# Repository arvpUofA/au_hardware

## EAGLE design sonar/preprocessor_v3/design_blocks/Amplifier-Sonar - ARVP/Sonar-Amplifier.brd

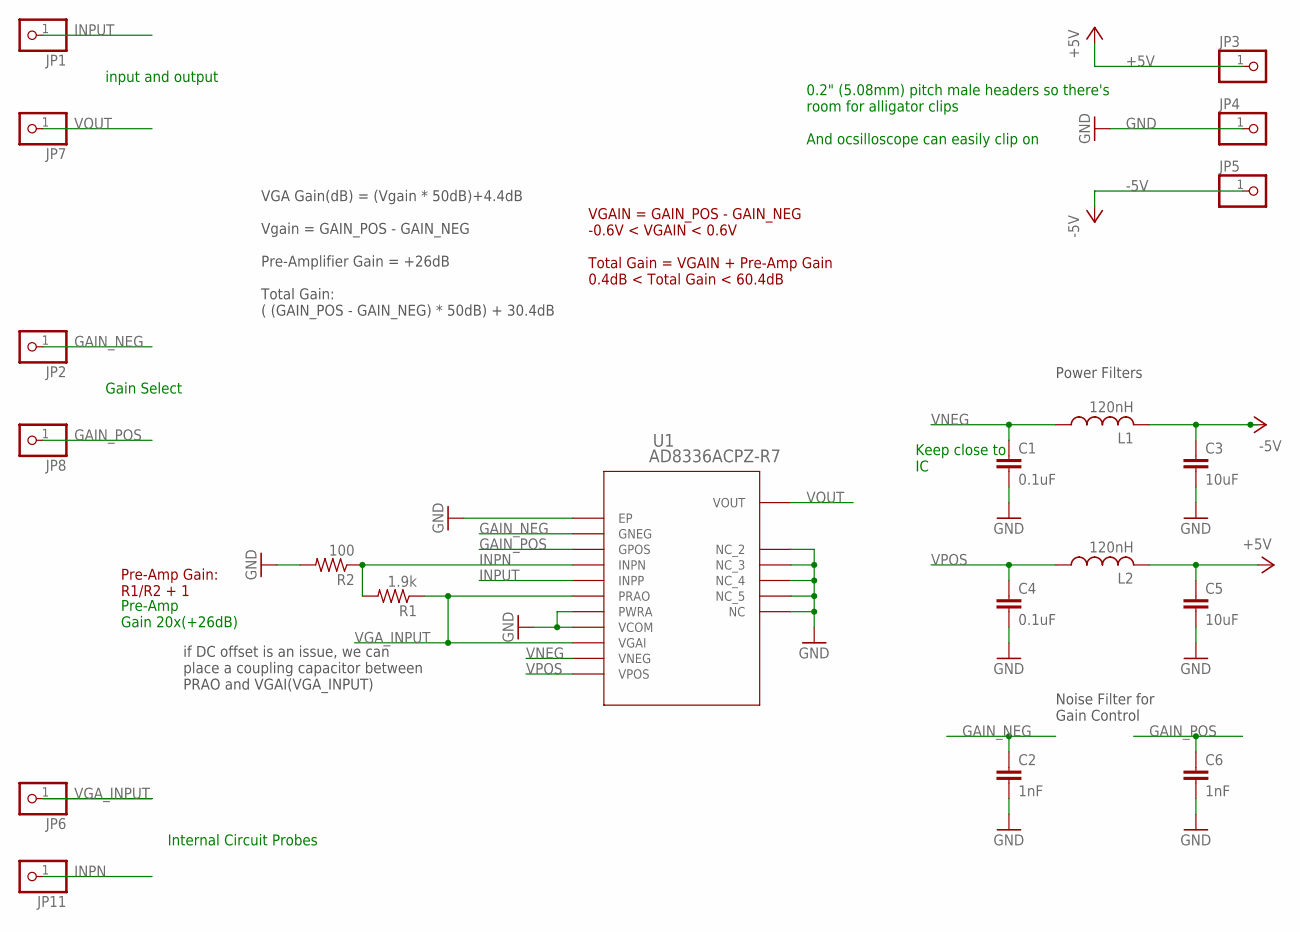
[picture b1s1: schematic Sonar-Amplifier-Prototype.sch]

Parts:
C1, C4: 0.1uF; C0603
C2, C6: 1nF; C0603
C3, C5: 10uF; C1206
JP1, JP2, JP3, JP4, JP5, JP6, JP7, JP8, JP11: PINHD-1X1; 1X01
L1, L2: 120nH; L3225P
R1: 1.9k; R0603
R2: 100; R0603
U1: AD8336ACPZ-R7; CP_16_4

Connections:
+5V: C5.1, JP3.1, L2.2
-5V: C3.1, JP5.1, L1.2
GAIN_NEG: C2.1, JP2.1, U1.GNEG
GAIN_POS: C6.1, JP8.1, U1.GPOS
GND: C1.2, C2.2, C3.2, C4.2, C5.2, C6.2, JP4.1, R2.2, U1.GND1 (EP), U1.NC, U1.NC1 (NC_2), U1.NC2 (NC_3), U1.NC3 (NC_4), U1.NC4 (NC_5), U1.PWRA, U1.VCOM
INPN: JP11.1, R1.2, R2.1, U1.INPN
INPUT: JP1.1, U1.INPP
VGA_INPUT: JP6.1, R1.1, U1.PRAO, U1.VGAI
VNEG: C1.1, L1.1, U1.VNEG
VOUT: JP7.1, U1.VOUT
VPOS: C4.1, L2.1, U1.VPOS

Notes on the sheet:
Pre-Amp Gain 20x(+26dB)
Power Filters
Keep close to IC
Noise Filter for Gain Control
0.2" (5.08mm) pitch male headers so there's room for alligator clips And ocsilloscope can easily clip on
input and output
Pre-Amp Gain: R1/R2 + 1
if DC offset is an issue, we can place a coupling capacitor between PRAO and VGAI(VGA_INPUT)
Gain Select
VGA Gain(dB) = (Vgain * 50dB)+4.4dB Vgain = GAIN_POS - GAIN_NEG Pre-Amplifier Gain = +26dB Total Gain: ( (GAIN_POS - GAIN_NEG) * 50dB) + 30.4dB
VGAIN = GAIN_POS - GAIN_NEG -0.6V < VGAIN < 0.6V Total Gain = VGAIN + Pre-Amp Gain 0.4dB < Total Gain < 60.4dB
Internal Circuit Probes

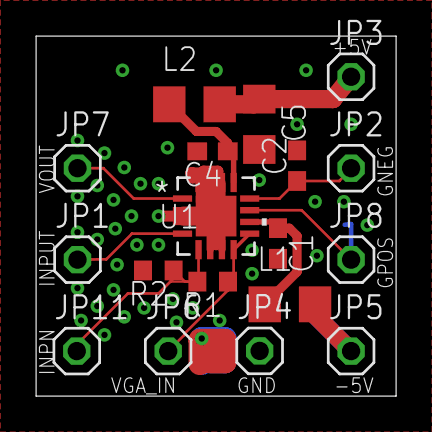
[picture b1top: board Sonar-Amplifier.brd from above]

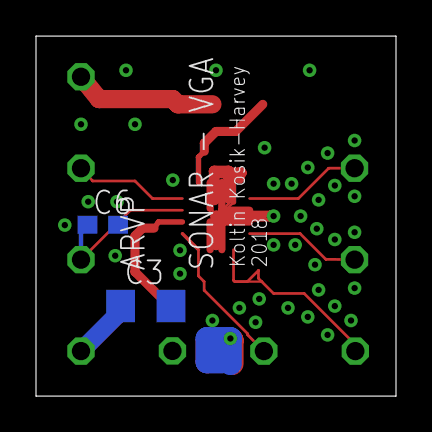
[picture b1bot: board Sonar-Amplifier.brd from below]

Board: 2 copper layers, 20.0 x 20.0 mm, 20 parts (2 on the bottom side), 11 nets.

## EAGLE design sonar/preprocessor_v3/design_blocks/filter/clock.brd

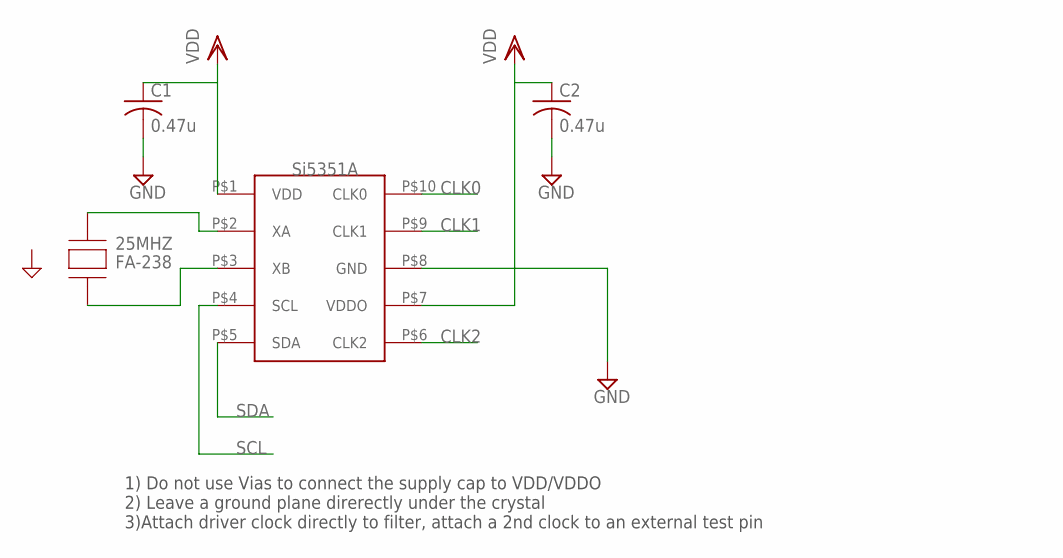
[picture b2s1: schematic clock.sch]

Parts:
25MHZ: FA-238
C1, C2: 0.47u; C0805
U$2: SI5351A; MSOP-10

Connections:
CLK0: U$2.P$10 (CLK0)
CLK1: U$2.P$9 (CLK1)
CLK2: U$2.P$6 (CLK2)
GND: C1.2, C2.2, U$2.P$8 (GND)
unnamed: 25MHZ.P$4 (XA), U$2.P$2 (XA)
unnamed: 25MHZ.P$2 (XB), U$2.P$3 (XB)
SCL: U$2.P$4 (SCL)
SDA: U$2.P$5 (SDA)
VDD: C1.1, C2.1, U$2.P$1 (VDD), U$2.P$7 (VDDO)

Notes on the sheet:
1) Do not use Vias to connect the supply cap to VDD/VDDO 2) Leave a ground plane direrectly under the crystal 3)Attach driver clock directly to filter, attach a 2nd clock to an external test pin

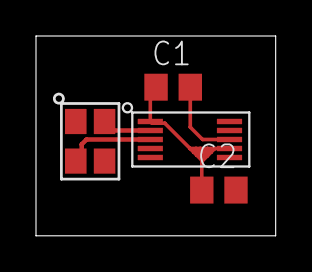
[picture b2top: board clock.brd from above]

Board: 2 copper layers, 13.3 x 11.1 mm, 4 parts (0 on the bottom side), 4 nets.

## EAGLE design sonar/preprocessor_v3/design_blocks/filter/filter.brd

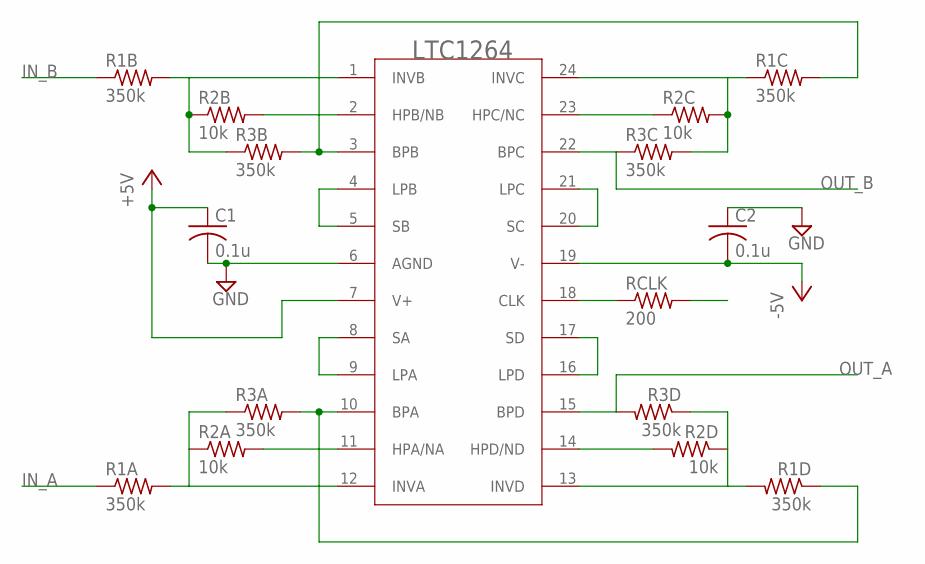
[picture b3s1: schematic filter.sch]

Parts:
C1, C2: 0.1u; C0805
R1A, R1B, R1C, R1D, R3A, R3B, R3C, R3D: 350k; R0805
R2A, R2B, R2C, R2D: 10k; R0805
RCLK: 200; R0805
U$1: LTC1264SMD; SO24W

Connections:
+5V: C1.1, U$1.7 (V+)
-5V: C2.2, U$1.19 (V-)
CLK: RCLK.2
GND: C1.2, C2.1, U$1.6 (AGND)
IN_A: R1A.1
IN_B: R1B.1
unnamed: R2D.2, U$1.14 (HPD/ND)
unnamed: R1D.2, R2D.1, R3D.1, U$1.13 (INVD)
unnamed: U$1.16 (LPD), U$1.17 (SD)
unnamed: R2C.1, U$1.23 (HPC/NC)
unnamed: R1C.1, R2C.2, R3C.2, U$1.24 (INVC)
unnamed: R2B.2, U$1.2 (HPB/NB)
unnamed: R1B.2, R2B.1, R3B.1, U$1.1 (INVB)
unnamed: U$1.4 (LPB), U$1.5 (SB)
unnamed: U$1.20 (SC), U$1.21 (LPC)
unnamed: RCLK.1, U$1.18 (CLK)
unnamed: R2A.2, U$1.11 (HPA/NA)
unnamed: U$1.8 (SA), U$1.9 (LPA)
unnamed: R1A.2, R2A.1, R3A.1, U$1.12 (INVA)
OUT_2ND_A: R1D.1, R3A.2, U$1.10 (BPA)
OUT_2ND_ORDER_B: R1C.2, R3B.2, U$1.3 (BPB)
OUT_A: R3D.2, U$1.15 (BPD)
OUT_B: R3C.1, U$1.22 (BPC)

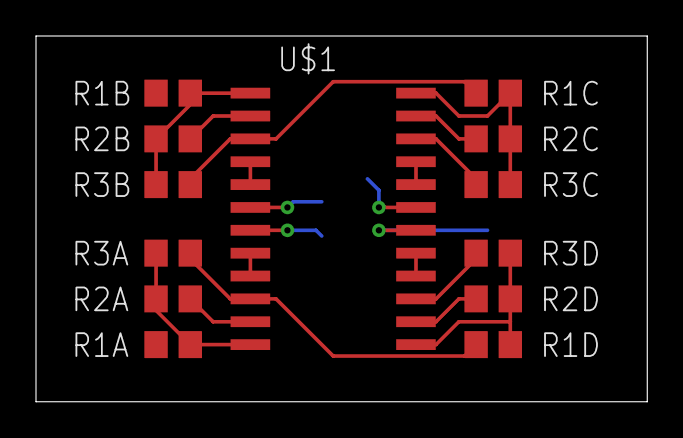
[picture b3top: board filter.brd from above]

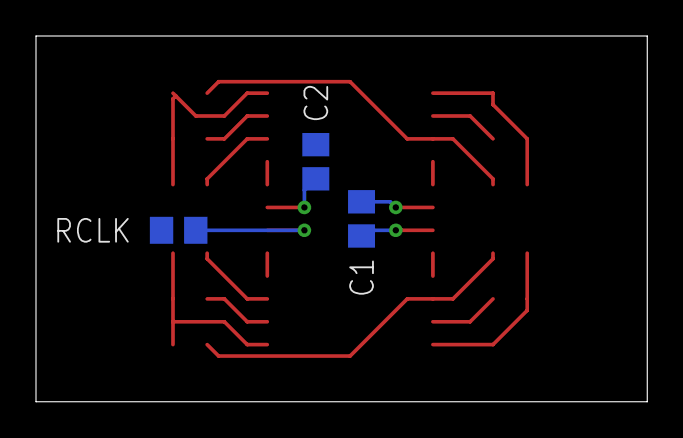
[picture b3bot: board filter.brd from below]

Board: 2 copper layers, 34.0 x 20.3 mm, 16 parts (3 on the bottom side), 20 nets.

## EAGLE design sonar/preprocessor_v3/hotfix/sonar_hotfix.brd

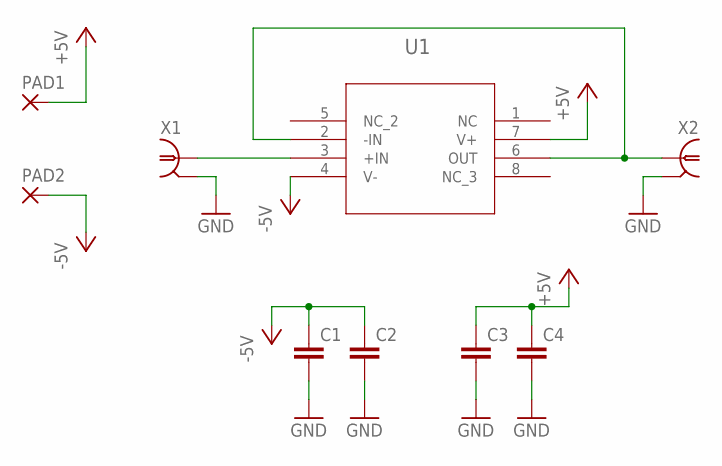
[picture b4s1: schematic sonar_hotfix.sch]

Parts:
C1, C2, C3, C4: C-EUC0603; C0603
PAD1, PAD2: WIREPADSMD5-2,5; 5-2,5
U1: LTC6240SO-8; SO-8
X1, X2: 0731000105

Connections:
+5V: C3.1, C4.1, PAD1.1, U1.7 (V+)
-5V: C1.1, C2.1, PAD2.1, U1.4 (V-)
GND: C1.2, C2.2, C3.2, C4.2, X1.P$1 (2), X1.P$2 (2), X2.P$1 (2), X2.P$2 (2)
unnamed: U1.3 (+IN), X1.P$3 (1)
unnamed: U1.2 (-IN), U1.6 (OUT), X2.P$3 (1)

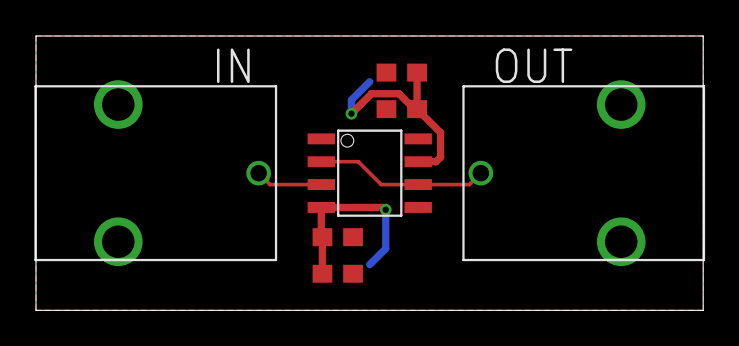
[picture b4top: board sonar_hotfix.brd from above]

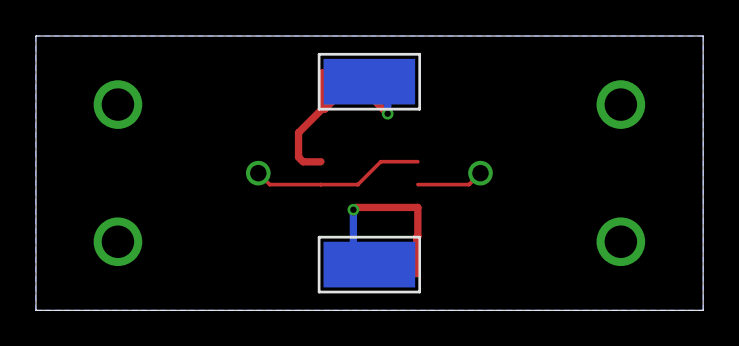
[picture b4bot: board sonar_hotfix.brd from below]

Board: 2 copper layers, 37.1 x 15.2 mm, 9 parts (2 on the bottom side), 5 nets.

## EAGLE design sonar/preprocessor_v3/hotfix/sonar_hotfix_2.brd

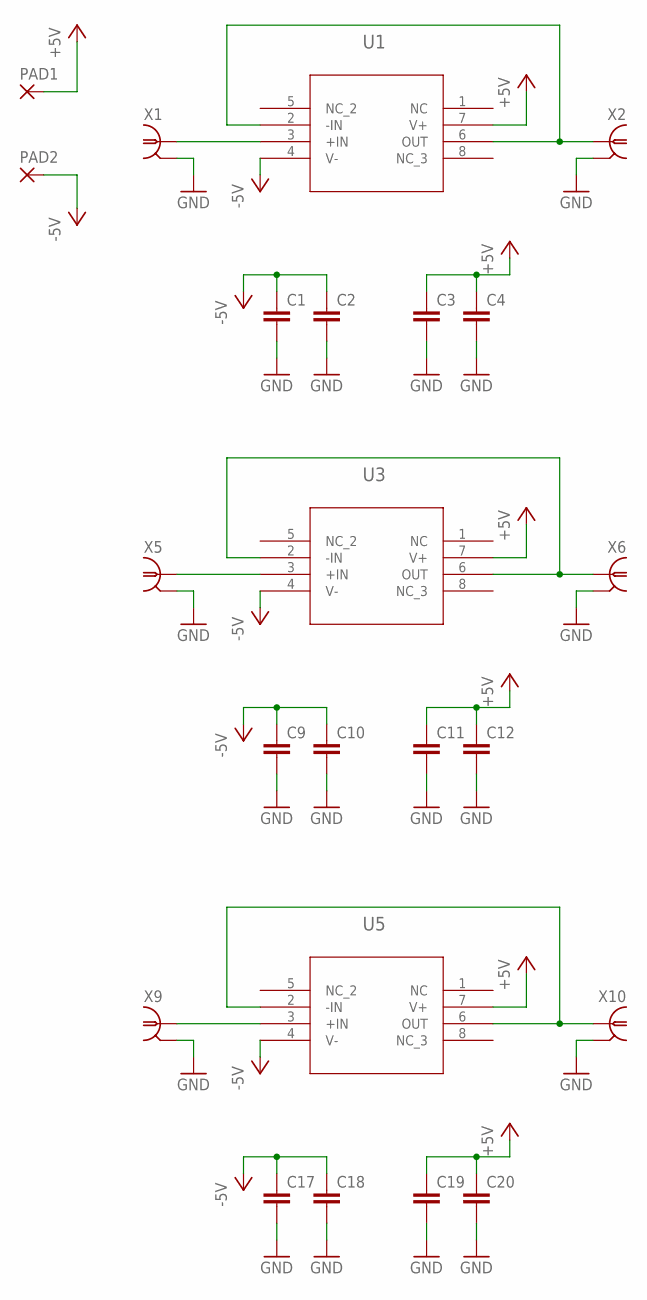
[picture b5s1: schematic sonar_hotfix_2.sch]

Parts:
C1, C2, C3, C4, C9, C10, C11, C12, C17, C18, C19, C20: C-EUC0603; C0603
PAD1, PAD2: WIREPADSMD5-2,5; 5-2,5
U1, U3, U5: LTC6240SO-8; SO-8
X1, X2, X5, X6, X9, X10: 0731000105

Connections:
+5V: C3.1, C4.1, C11.1, C12.1, C19.1, C20.1, PAD1.1, U1.7 (V+), U3.7 (V+), U5.7 (V+)
-5V: C1.1, C2.1, C9.1, C10.1, C17.1, C18.1, PAD2.1, U1.4 (V-), U3.4 (V-), U5.4 (V-)
GND: C1.2, C2.2, C3.2, C4.2, C9.2, C10.2, C11.2, C12.2, C17.2, C18.2, C19.2, C20.2, X1.P$1 (2), X1.P$2 (2), X2.P$1 (2), X2.P$2 (2), X5.P$1 (2), X5.P$2 (2), X6.P$1 (2), X6.P$2 (2), X9.P$1 (2), X9.P$2 (2), X10.P$1 (2), X10.P$2 (2)
unnamed: U1.3 (+IN), X1.P$3 (1)
unnamed: U1.2 (-IN), U1.6 (OUT), X2.P$3 (1)
unnamed: U3.3 (+IN), X5.P$3 (1)
unnamed: U3.2 (-IN), U3.6 (OUT), X6.P$3 (1)
unnamed: U5.3 (+IN), X9.P$3 (1)
unnamed: U5.2 (-IN), U5.6 (OUT), X10.P$3 (1)

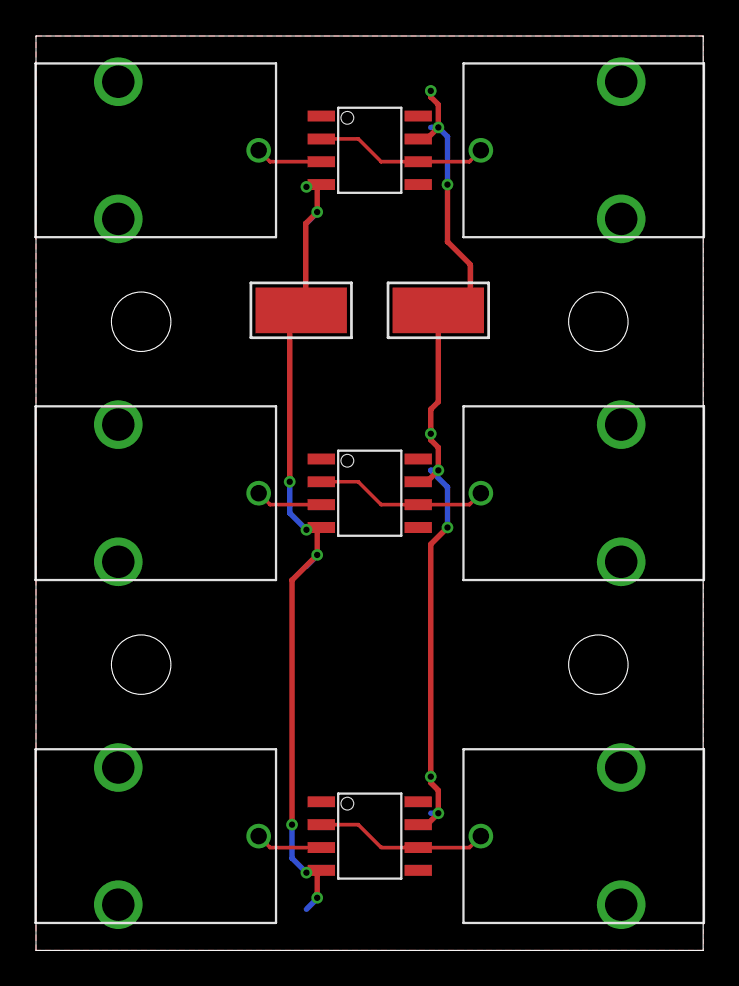
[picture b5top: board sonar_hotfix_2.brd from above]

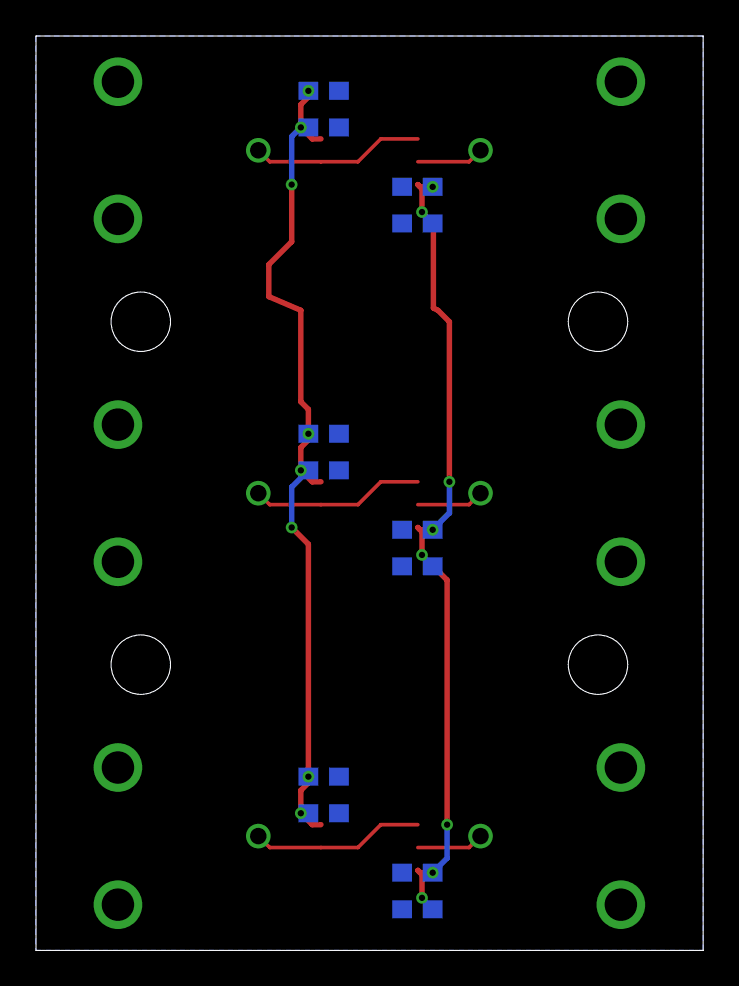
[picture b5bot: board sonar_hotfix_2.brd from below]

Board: 2 copper layers, 37.1 x 50.8 mm, 27 parts (12 on the bottom side), 9 nets.

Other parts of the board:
U$1, U$2, U$3, U$4: STAND-OFF

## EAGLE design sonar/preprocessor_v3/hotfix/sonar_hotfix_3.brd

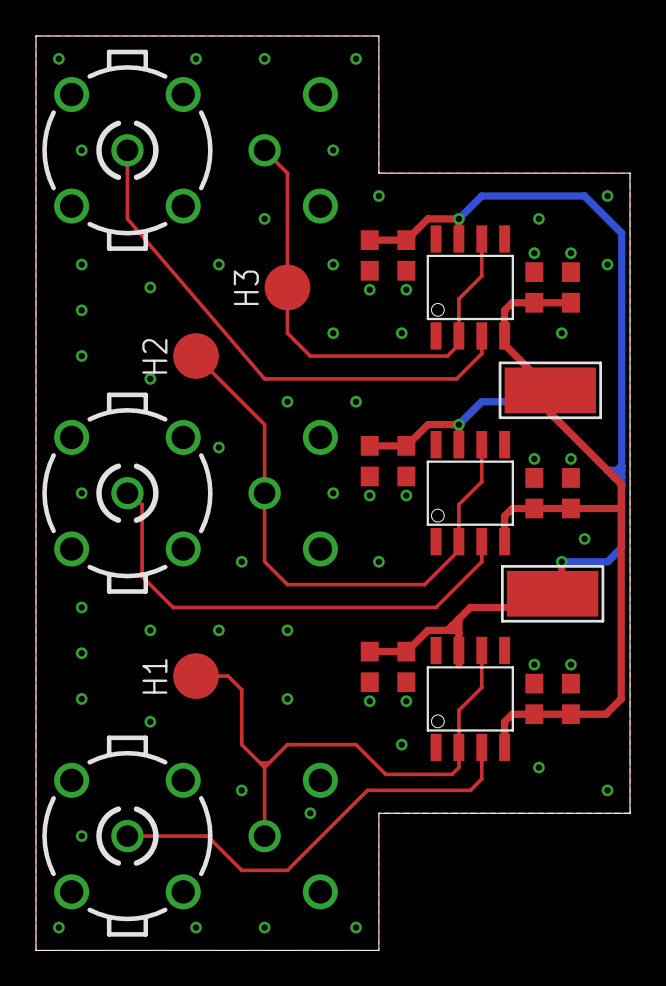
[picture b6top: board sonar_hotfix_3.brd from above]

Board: 2 copper layers, 33.0 x 50.8 mm, 26 parts (0 on the bottom side), 9 nets.

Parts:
C1, C2, C3, C4, C5, C6, C7, C8, C9, C10, C11, C12: C0603
H1, H2, H3: TPB2,54; B2,54
PAD1, PAD2: WIREPADSMD5-2,5; 5-2,5
U1, U2, U3: SO-8
X1, X2, X3: BN35N61; B35N61
X4, X5, X6: B35N61-HALF

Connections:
+5V: C7.1, C8.1, C9.1, C10.1, C11.1, C12.1, PAD1.1, U1.7, U2.7, U3.7
-5V: C1.1, C2.1, C3.1, C4.1, C5.1, C6.1, PAD2.1, U1.4, U2.4, U3.4
GND: C1.2, C2.2, C3.2, C4.2, C5.2, C6.2, C7.2, C8.2, C9.2, C10.2, C11.2, C12.2, X1.2, X1.3, X1.4, X1.5, X2.2, X2.3, X2.4, X2.5, X3.2, X3.3, X3.4, X3.5, X4.2, X4.3, X5.2, X5.3, X6.2, X6.3
unnamed: U1.3, X1.1
unnamed: H3.TP, U1.2, U1.6, X4.1
unnamed: U2.3, X2.1
unnamed: H2.TP, U2.2, U2.6, X5.1
unnamed: U3.3, X3.1
unnamed: H1.TP, U3.2, U3.6, X6.1

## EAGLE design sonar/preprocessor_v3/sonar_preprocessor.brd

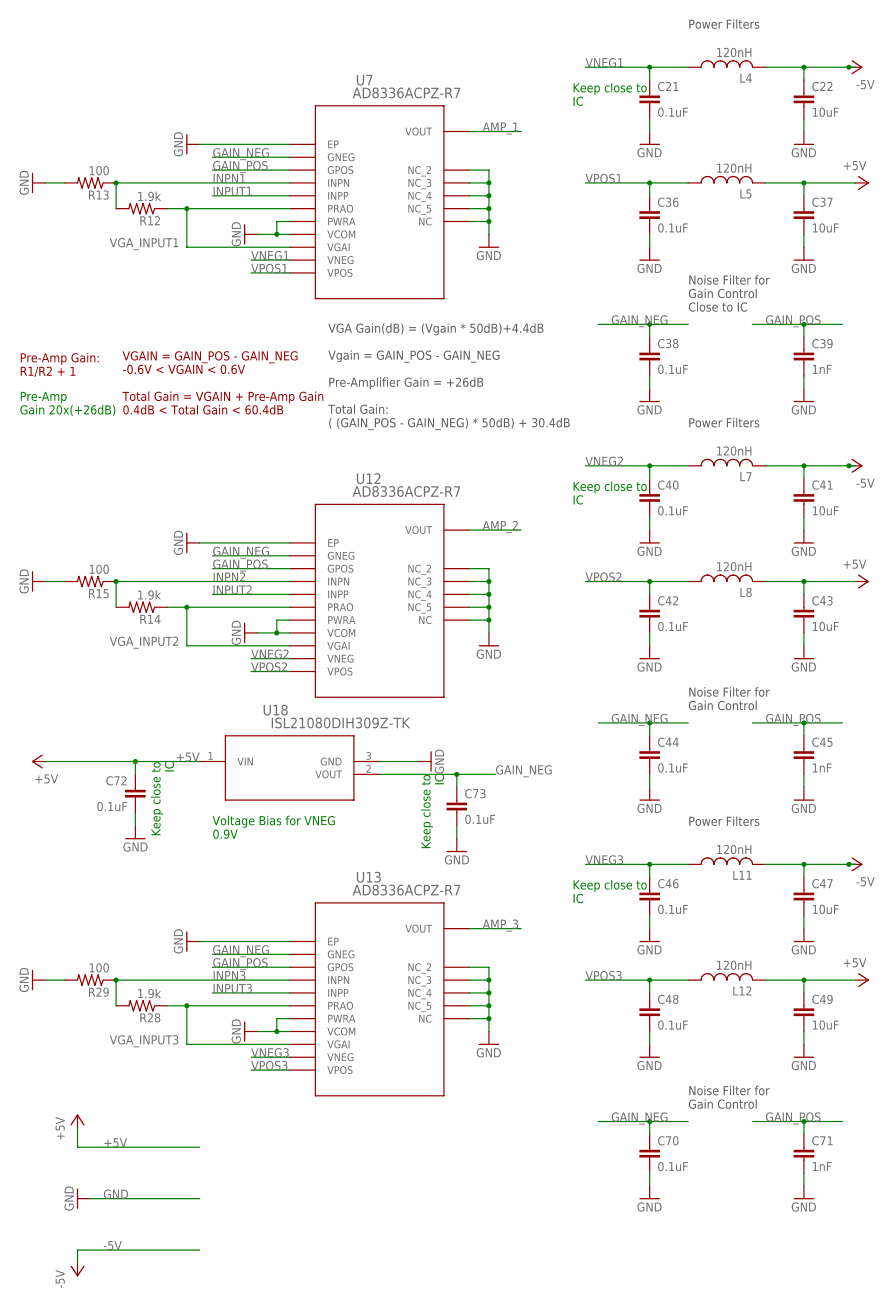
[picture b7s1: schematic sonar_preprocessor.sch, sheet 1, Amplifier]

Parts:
C21, C36, C38, C40, C42, C44, C46, C48, C70, C72, C73: 0.1uF; C0603
C22, C37, C41, C43, C47, C49: 10uF; C1206
C39, C45, C71: 1nF; C0603
L4, L5, L7, L8, L11, L12: 120nH; L3225P
R12, R14, R28: 1.9k; R0603
R13, R15, R29: 100; R0603
U7, U12, U13: AD8336ACPZ-R7; CP_16_4
U18: ISL21080DIH309Z-TK; P3_064

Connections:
+5V: C37.1, C43.1, C49.1, C72.1, L5.2, L8.2, L12.2, U18.1 (VIN); also elsewhere on the board
-5V: C22.1, C41.1, C47.1, L4.2, L7.2, L11.2; also elsewhere on the board
AMP_1: U7.VOUT; also elsewhere on the board
AMP_2: U12.VOUT; also elsewhere on the board
AMP_3: U13.VOUT; also elsewhere on the board
GAIN_NEG: C38.1, C44.1, C70.1, C73.1, U7.GNEG, U12.GNEG, U13.GNEG, U18.2 (VOUT)
GAIN_POS: C39.1, C45.1, C71.1, U7.GPOS, U12.GPOS, U13.GPOS; also elsewhere on the board
GND: C21.2, C22.2, C36.2, C37.2, C38.2, C39.2, C40.2, C41.2, C42.2, C43.2, C44.2, C45.2, C46.2, C47.2, C48.2, C49.2, C70.2, C71.2, C72.2, C73.2, R13.2, R15.2, R29.2, U7.GND1 (EP), U7.NC, U7.NC1 (NC_2), U7.NC2 (NC_3), U7.NC3 (NC_4), U7.NC4 (NC_5), U7.PWRA, U7.VCOM, U12.GND1 (EP), U12.NC, U12.NC1 (NC_2), U12.NC2 (NC_3), U12.NC3 (NC_4), U12.NC4 (NC_5), U12.PWRA, U12.VCOM, U13.GND1 (EP), U13.NC, U13.NC1 (NC_2), U13.NC2 (NC_3), U13.NC3 (NC_4), U13.NC4 (NC_5), U13.PWRA, U13.VCOM, U18.3 (GND); also elsewhere on the board
INPN1: R12.2, R13.1, U7.INPN
INPN2: R14.2, R15.1, U12.INPN
INPN3: R28.2, R29.1, U13.INPN
INPUT1: U7.INPP; also elsewhere on the board
INPUT2: U12.INPP; also elsewhere on the board
INPUT3: U13.INPP; also elsewhere on the board
VGA_INPUT1: R12.1, U7.PRAO, U7.VGAI
VGA_INPUT2: R14.1, U12.PRAO, U12.VGAI
VGA_INPUT3: R28.1, U13.PRAO, U13.VGAI
VNEG1: C21.1, L4.1, U7.VNEG
VNEG2: C40.1, L7.1, U12.VNEG
VNEG3: C46.1, L11.1, U13.VNEG
VPOS1: C36.1, L5.1, U7.VPOS
VPOS2: C42.1, L8.1, U12.VPOS
VPOS3: C48.1, L12.1, U13.VPOS

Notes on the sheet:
Pre-Amp Gain 20x(+26dB)
Power Filters
Keep close to IC
Noise Filter for Gain Control Close to IC
Pre-Amp Gain: R1/R2 + 1
VGA Gain(dB) = (Vgain * 50dB)+4.4dB Vgain = GAIN_POS - GAIN_NEG Pre-Amplifier Gain = +26dB Total Gain: ( (GAIN_POS - GAIN_NEG) * 50dB) + 30.4dB
VGAIN = GAIN_POS - GAIN_NEG -0.6V < VGAIN < 0.6V Total Gain = VGAIN + Pre-Amp Gain 0.4dB < Total Gain < 60.4dB
Noise Filter for Gain Control
Voltage Bias for VNEG 0.9V

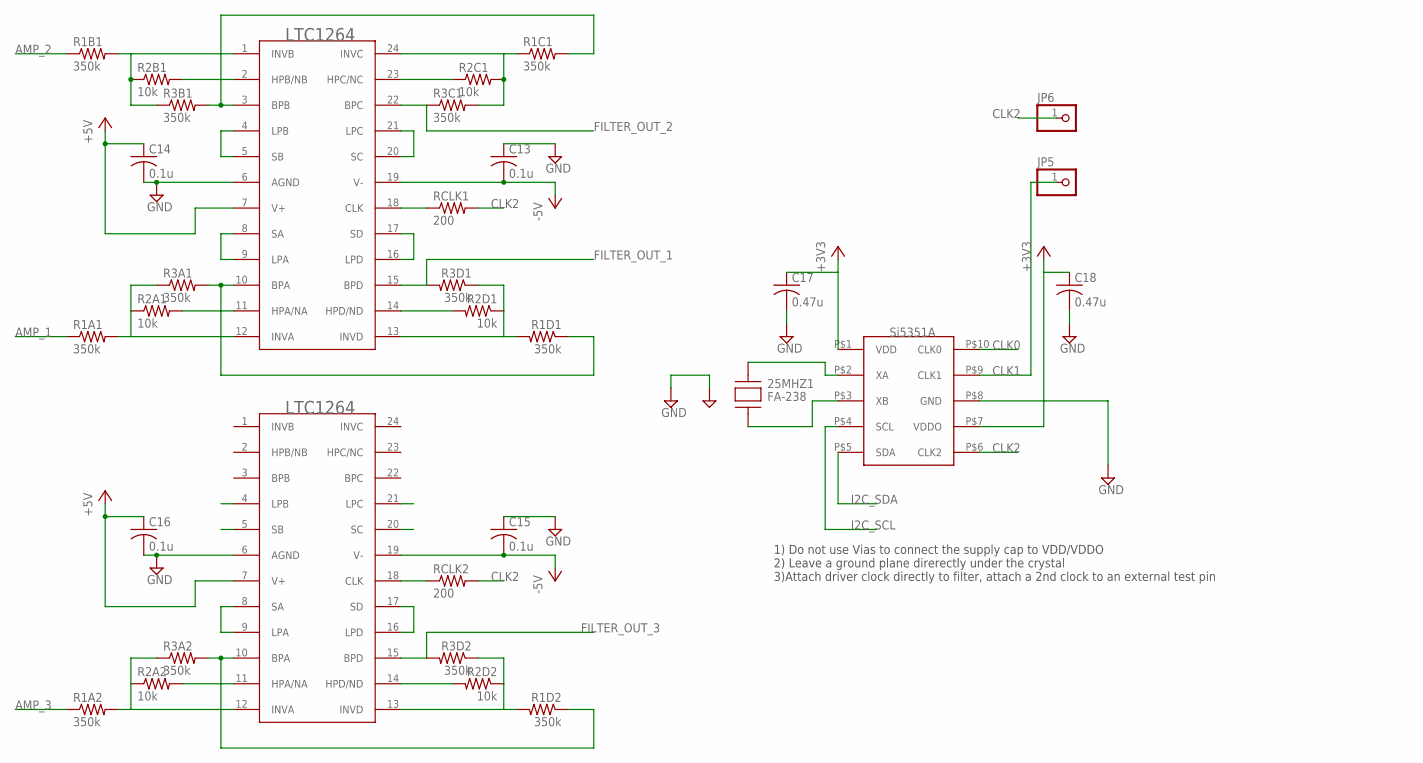
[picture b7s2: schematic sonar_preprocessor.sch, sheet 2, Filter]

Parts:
25MHZ1: FA-238
C13, C14, C15, C16: 0.1u; C0805
C17, C18: 0.47u; C0805
JP5, JP6: PINHD-1X1; 1X01
R1A1, R1A2, R1B1, R1C1, R1D1, R1D2, R3A1, R3A2, R3B1, R3C1, R3D1, R3D2: 350k; R0805
R2A1, R2A2, R2B1, R2C1, R2D1, R2D2: 10k; R0805
RCLK1, RCLK2: 200; R0805
U$6, U$7: LTC1264SMD; SO24W
U$8: SI5351A; MSOP-10

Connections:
+3V3: C17.1, C18.1, U$8.P$1 (VDD), U$8.P$7 (VDDO); also elsewhere on the board
+5V: C14.1, C16.1, U$6.7 (V+), U$7.7 (V+); also elsewhere on the board
-5V: C13.2, C15.2, U$6.19 (V-), U$7.19 (V-); also elsewhere on the board
AMP_1: R1A1.1; also elsewhere on the board
AMP_2: R1B1.1; also elsewhere on the board
AMP_3: R1A2.1; also elsewhere on the board
CLK0: U$8.P$10 (CLK0)
CLK1: JP5.1, U$8.P$9 (CLK1)
CLK2: JP6.1, RCLK1.2, RCLK2.2, U$8.P$6 (CLK2)
FILTER_OUT_1: R3D1.2, U$6.15 (BPD); also elsewhere on the board
FILTER_OUT_2: R3C1.1, U$6.22 (BPC); also elsewhere on the board
FILTER_OUT_3: R3D2.2, U$7.15 (BPD); also elsewhere on the board
GND: 25MHZ1.P$1 (GND), 25MHZ1.P$3 (GND), C13.1, C14.2, C15.1, C16.2, C17.2, C18.2, U$6.6 (AGND), U$7.6 (AGND), U$8.P$8 (GND); also elsewhere on the board
I2C_SCL: U$8.P$4 (SCL); also elsewhere on the board
I2C_SDA: U$8.P$5 (SDA); also elsewhere on the board
unnamed: 25MHZ1.P$4 (XA), U$8.P$2 (XA)
unnamed: 25MHZ1.P$2 (XB), U$8.P$3 (XB)
unnamed: R2A1.2, U$6.11 (HPA/NA)
unnamed: U$6.8 (SA), U$6.9 (LPA)
unnamed: R1A1.2, R2A1.1, R3A1.1, U$6.12 (INVA)
unnamed: R2D1.2, U$6.14 (HPD/ND)
unnamed: R1D1.2, R2D1.1, R3D1.1, U$6.13 (INVD)
unnamed: U$6.16 (LPD), U$6.17 (SD)
unnamed: R2C1.1, U$6.23 (HPC/NC)
unnamed: R1C1.1, R2C1.2, R3C1.2, U$6.24 (INVC)
unnamed: R2B1.2, U$6.2 (HPB/NB)
unnamed: R1B1.2, R2B1.1, R3B1.1, U$6.1 (INVB)
unnamed: U$6.4 (LPB), U$6.5 (SB)
unnamed: U$6.20 (SC), U$6.21 (LPC)
unnamed: RCLK1.1, U$6.18 (CLK)
unnamed: R2A2.2, U$7.11 (HPA/NA)
unnamed: U$7.8 (SA), U$7.9 (LPA)
unnamed: R1A2.2, R2A2.1, R3A2.1, U$7.12 (INVA)
unnamed: R2D2.2, U$7.14 (HPD/ND)
unnamed: R1D2.2, R2D2.1, R3D2.1, U$7.13 (INVD)
unnamed: U$7.16 (LPD), U$7.17 (SD)
unnamed: RCLK2.1, U$7.18 (CLK)
OUT_2ND_A1: R1D1.1, R3A1.2, U$6.10 (BPA)
OUT_2ND_A2: R1D2.1, R3A2.2, U$7.10 (BPA)
OUT_2ND_ORDER_B1: R1C1.2, R3B1.2, U$6.3 (BPB)

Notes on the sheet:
1) Do not use Vias to connect the supply cap to VDD/VDDO 2) Leave a ground plane direrectly under the crystal 3)Attach driver clock directly to filter, attach a 2nd clock to an external test pin

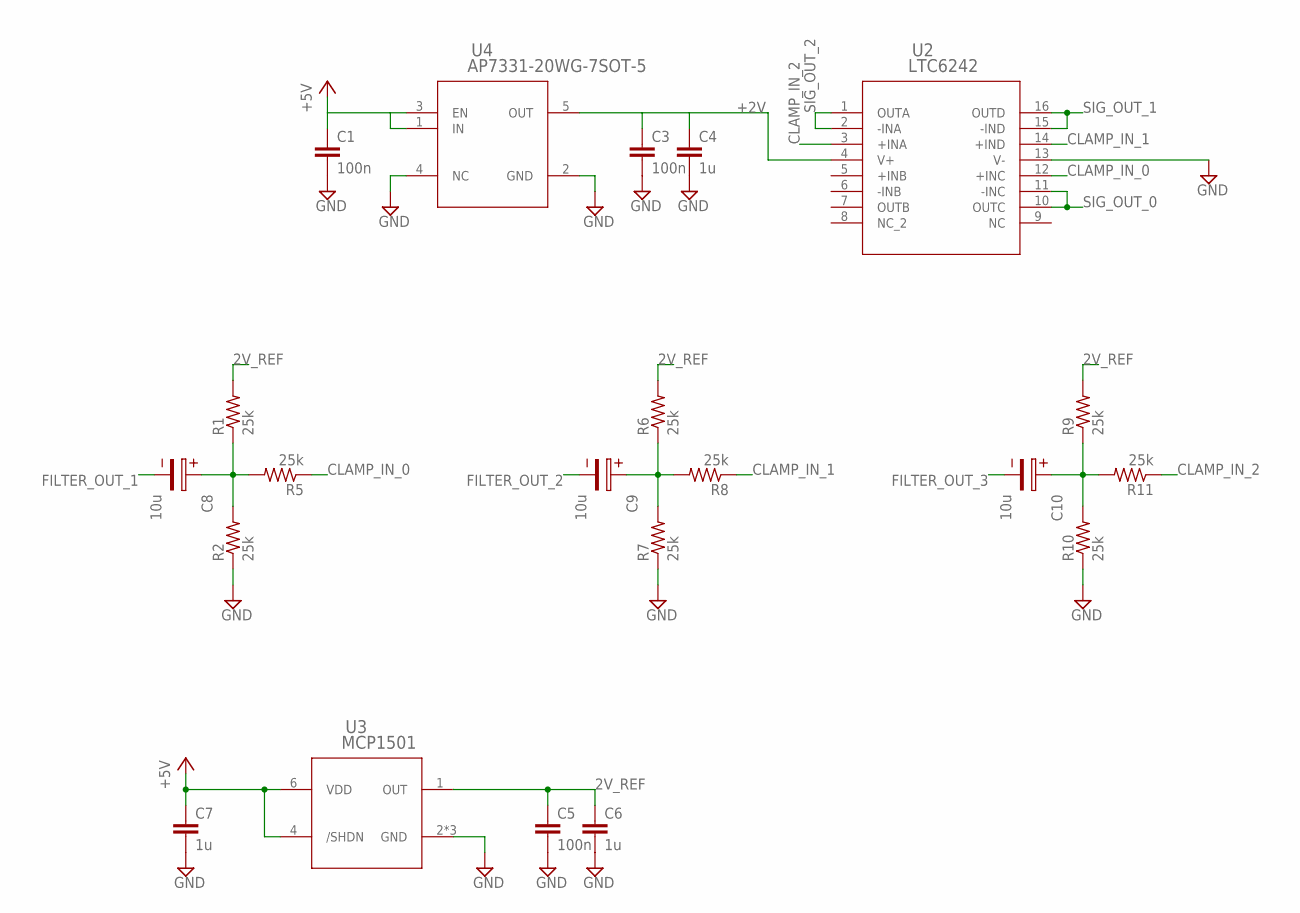
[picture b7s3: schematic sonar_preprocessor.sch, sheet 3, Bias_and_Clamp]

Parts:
C1, C3, C5: 100n; C0805
C4, C6, C7: 1u; C0805
C8, C9, C10: 10u; 2.6X1.6X1(BXCXA)
R1, R2, R5, R6, R7, R8, R9, R10, R11: 25k; R0805
U2: LTC6242; SSOP16
U3: MCP1501; SOT23-6
U4: AP7331-20WG-7SOT-5; SOT23-5

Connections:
2V_REF: C5.1, C6.1, R1.2, R6.2, R9.2, U3.1 (OUT)
+2V: C3.1, C4.1, U2.4 (V+), U4.5 (OUT)
+5V: C1.1, C7.1, U3.4 (/SHDN), U3.6 (VDD), U4.1 (IN), U4.3 (EN); also elsewhere on the board
BIASED_0: C8.1, R1.1, R2.2, R5.2
BIASED_1: C9.1, R6.1, R7.2, R8.2
BIASED_2: C10.1, R9.1, R10.2, R11.2
CLAMP_IN_0: R5.1, U2.12 (+INC)
CLAMP_IN_1: R8.1, U2.14 (+IND)
CLAMP_IN_2: R11.1, U2.3 (+INA)
FILTER_OUT_1: C8.2; also elsewhere on the board
FILTER_OUT_2: C9.2; also elsewhere on the board
FILTER_OUT_3: C10.2; also elsewhere on the board
GND: C1.2, C3.2, C4.2, C5.2, C6.2, C7.2, R2.1, R7.1, R10.1, U2.13 (V-), U3.2 (GND), U3.3 (GND), U3.5 (GND), U4.2 (GND), U4.4 (NC); also elsewhere on the board
SIG_OUT_0: U2.10 (OUTC), U2.11 (-INC); also elsewhere on the board
SIG_OUT_1: U2.15 (-IND), U2.16 (OUTD); also elsewhere on the board
SIG_OUT_2: U2.1 (OUTA), U2.2 (-INA); also elsewhere on the board

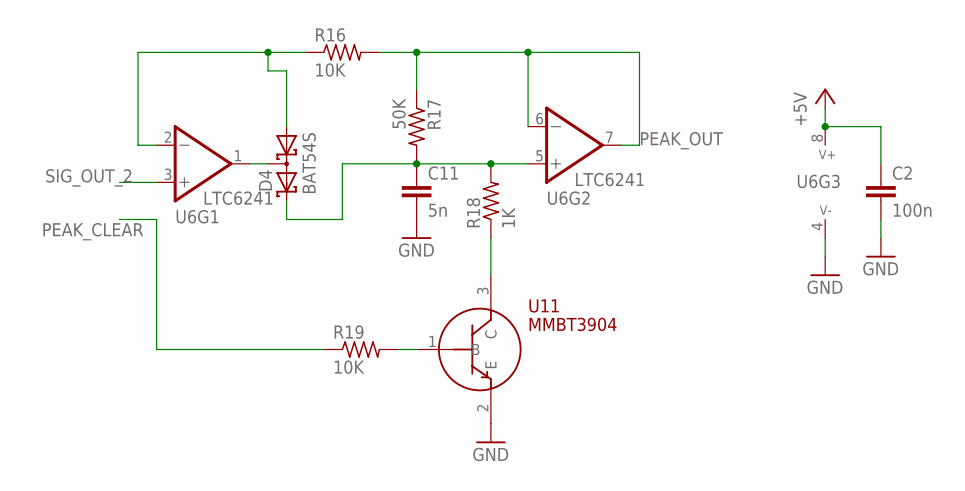
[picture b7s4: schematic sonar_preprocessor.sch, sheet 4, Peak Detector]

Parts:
C2: 100n; C0805
C11: 5n; C0805
D4: BAT54S; SOT23
R16, R19: 10K; R0805
R17: 50K; R0805
R18: 1K; R0805
U6: LTC6241; SO-8
U11: MMBT3904; SOT23

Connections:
+5V: C2.1, U6.8 (V+); also elsewhere on the board
GND: C2.2, C11.2, U6.4 (V-), U11.2 (E); also elsewhere on the board
unnamed: C11.1, D4.2 (C2), R17.2, R18.2, U6.5 (+IN)
unnamed: D4.1 (A1), R16.1, U6.2 (-IN)
unnamed: D4.3 (C1A2), U6.1 (OUT)
unnamed: R19.2, U11.1 (B)
unnamed: R18.1, U11.3 (C)
PEAK_CLEAR: R19.1; also elsewhere on the board
PEAK_OUT: R16.2, R17.1, U6.6 (-IN), U6.7 (OUT); also elsewhere on the board
SIG_OUT_2: U6.3 (+IN); also elsewhere on the board

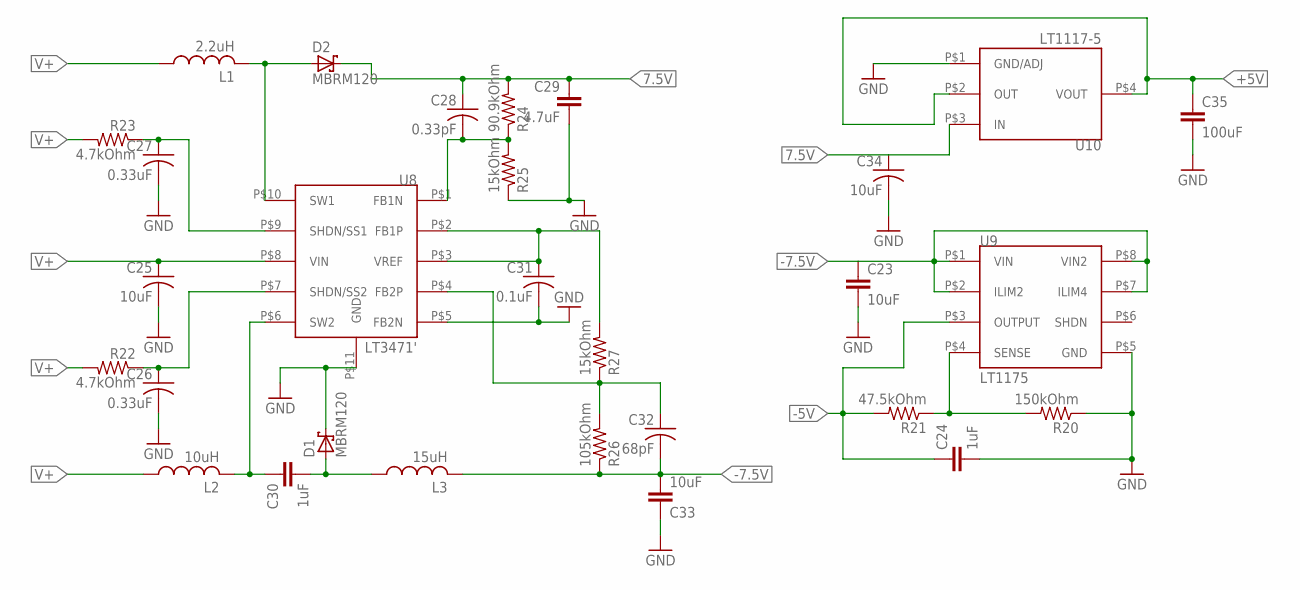
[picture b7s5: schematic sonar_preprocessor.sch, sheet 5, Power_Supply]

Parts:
C23, C33: 10uF; C0805
C24, C30: 1uF; C1206
C25, C34: 10uF; C0603
C26, C27: 0.33uF; C0603
C28: 0.33pF; C0603
C29: 4.7uF; C1206
C31: 0.1uF; C0603
C32: 68pF; C0603
C35: 100uF; C1210
D1, D2: MBRM120; DO-216AA
L1: 2.2uH; NS4.9X4.9
L2: 10uH; NS5X5
L3: 15uH; NS5X5
R20: 150kOhm; R0603
R21: 47.5kOhm; R0603
R22, R23: 4.7kOhm; R0603
R24: 90.9kOhm; R0603
R25, R27: 15kOhm; R0603
R26: 105kOhm; R0603
U8: LT3471'; 10-WFDFN
U9: LT1175; 8-SOIC
U10: LT1117-5; SOT233-3

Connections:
7.5V: C28.1, C29.1, C34.1, D2.P$1 (C), R24.2, U10.P$3 (IN)
+5V: C35.1, U10.P$2 (OUT), U10.P$4 (VOUT); also elsewhere on the board
-5V: C24.1, R21.2, U9.P$3 (OUTPUT); also elsewhere on the board
-7.5V: C23.1, C32.2, C33.2, L3.P$2 (2), R26.1, U9.P$1 (VIN), U9.P$2 (ILIM2), U9.P$7 (ILIM4), U9.P$8 (VIN2)
GND: C23.2, C24.2, C25.2, C26.2, C27.2, C29.2, C31.2, C33.1, C34.2, C35.2, D1.P$1 (C), R20.1, R25.1, U8.P$5 (FB2N), U8.P$11 (GND), U9.P$5 (GND), U10.P$1 (GND/ADJ); also elsewhere on the board
unnamed: R20.2, R21.1, U9.P$4 (SENSE)
unnamed: D2.P$2 (A), L1.P$2 (2), U8.P$10 (SW1)
unnamed: C28.2, R24.1, R25.2, U8.P$1 (FB1N)
unnamed: C30.1, L2.P$2 (2), U8.P$6 (SW2)
unnamed: C30.2, D1.P$2 (A), L3.P$1 (1)
unnamed: C32.1, R26.2, R27.1, U8.P$4 (FB2P)
SS3: C26.1, R22.1, U8.P$7 (SHDN/SS2)
SS4: C27.1, R23.1, U8.P$9 (SHDN/SS1)
V+: C25.1, L1.P$1 (1), L2.P$1 (1), R22.2, R23.2, U8.P$8 (VIN); also elsewhere on the board
VREF: C31.1, R27.2, U8.P$2 (FB1P), U8.P$3 (VREF)

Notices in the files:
parts and their libraries:
Kondensatoren: Copyright: Würth Elektronik
